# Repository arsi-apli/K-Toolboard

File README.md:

# K-Toolboard

3d printer toolboad for Klipper firmware. 
The toolboard consists of the injector board and the toolboard itself. 
An RPI FFC camera cable is used for the connection.
RS422 line is used for transmission and it is connected to the serial / USB converter on the injector board.

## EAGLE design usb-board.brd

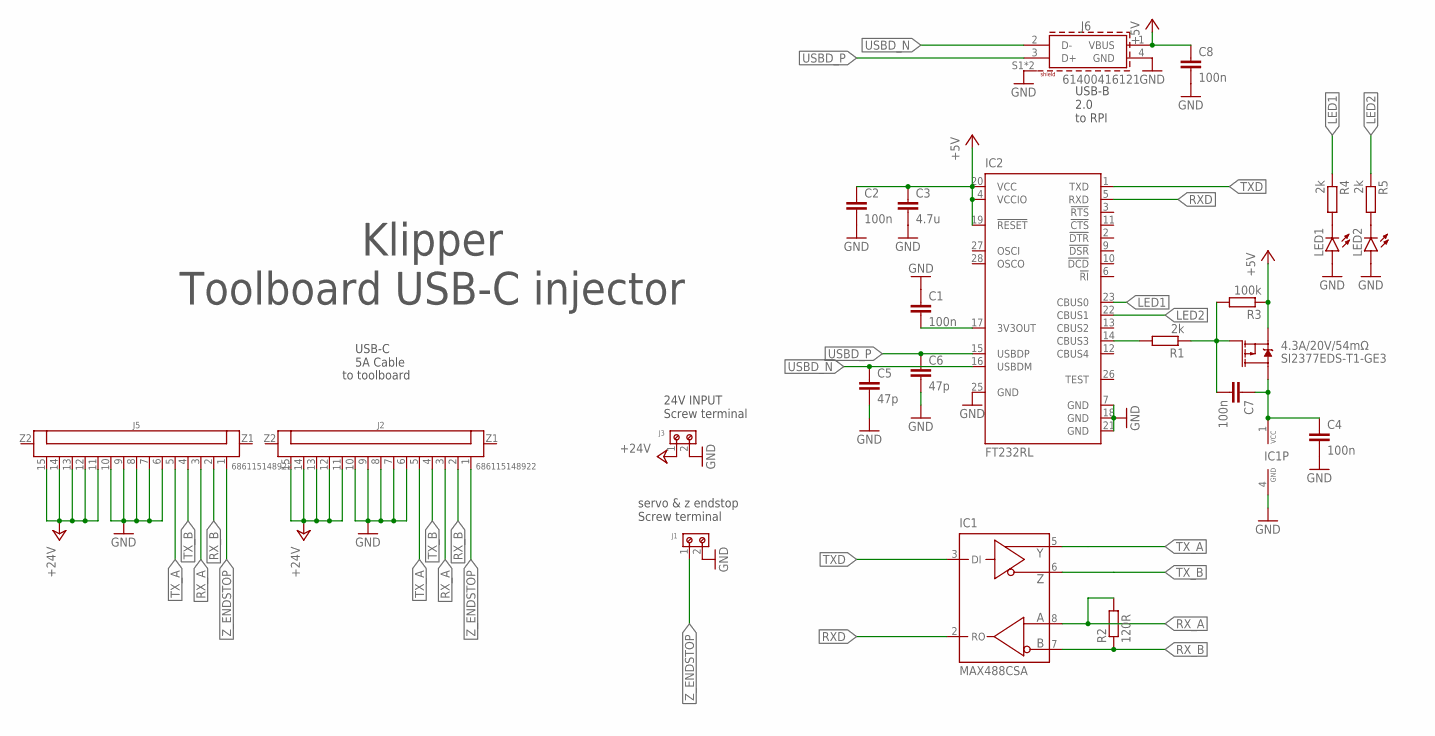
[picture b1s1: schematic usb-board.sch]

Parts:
C1, C2, C4, C7, C8: 100n; C0805
C3: 4.7u; C0805
C5, C6: 47p; C0805
IC1: MAX488CSA; SO08
IC2: FT232RL; SSOP28
J1, J3: 691103110002
J2, J5: 686115148922
J6: 61400416121
LED1, LED2: LEDCHIPLED_0805; CHIPLED_0805
R1, R4, R5: 2k; R0805
R2: 120R; R0805
R3: 100k; R0805
SI2377EDS-T1-GE3: 4.3A/20V/54mΩ; SOT23-3

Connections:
+5V: C2.1, C3.1, C8.1, IC2.4 (VCCIO), IC2.19 (!RESET), IC2.20 (VCC), J6.1 (VBUS), R3.1, SI2377EDS-T1-GE3.2 (S)
+24V: J2.11, J2.12, J2.13, J2.14, J2.15, J3.1, J5.11, J5.12, J5.13, J5.14, J5.15
GND: C1.1, C2.2, C3.2, C4.2, C5.2, C6.2, C8.2, IC1.4 (GND), IC2.7 (GND), IC2.18 (GND), IC2.21 (GND), IC2.25 (GND), J1.2, J2.6, J2.7, J2.8, J2.9, J2.10, J3.2, J5.6, J5.7, J5.8, J5.9, J5.10, J6.4 (GND), J6.S1 (SHIELD), J6.S2 (SHIELD), LED1.A, LED2.A
LED1: IC2.23 (CBUS0), R4.1
LED2: IC2.22 (CBUS1), R5.1
unnamed: C1.2, IC2.17 (3V3OUT)
unnamed: IC2.14 (CBUS3), R1.2
unnamed: C7.2, R1.1, R3.2, SI2377EDS-T1-GE3.1 (G)
unnamed: C4.1, C7.1, IC1.1 (VCC), SI2377EDS-T1-GE3.3 (D)
unnamed: LED1.C, R4.2
unnamed: LED2.C, R5.2
RXD: IC1.2 (RO), IC2.5 (RXD)
RX_A: IC1.8 (A), J2.3, J5.3, R2.2
RX_B: IC1.7 (B), J2.2, J5.2, R2.1
TXD: IC1.3 (DI), IC2.1 (TXD)
TX_A: IC1.5 (Y), J2.5, J5.5
TX_B: IC1.6 (Z), J2.4, J5.4
USBD_N: C5.1, IC2.16 (USBDM), J6.2 (D-)
USBD_P: C6.1, IC2.15 (USBDP), J6.3 (D+)
Z_ENDSTOP: J1.1, J2.1, J5.1

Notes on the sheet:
USB-C 5A Cable
to toolboard
24V INPUT Screw terminal
servo & z endstop Screw terminal
Klipper Toolboard USB-C injector
USB-B 2.0 to RPI

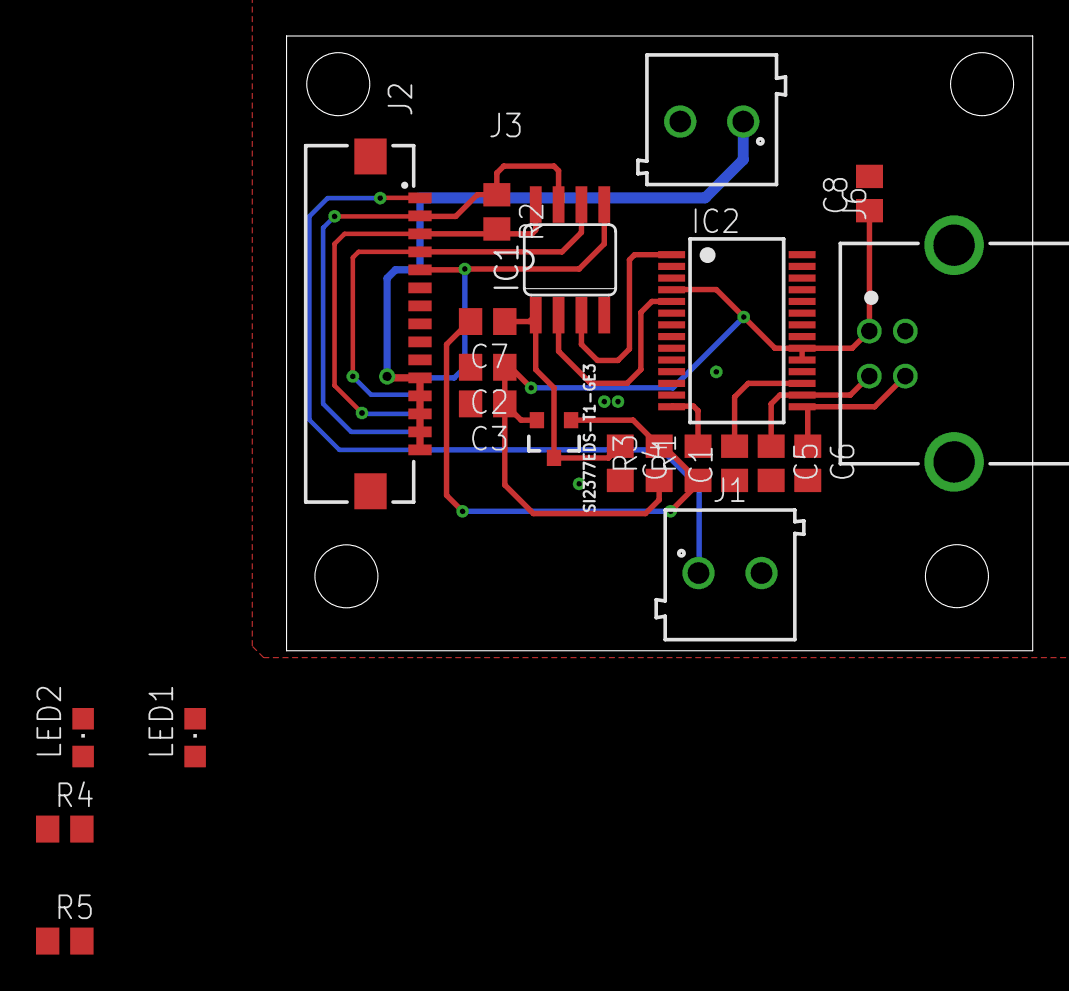
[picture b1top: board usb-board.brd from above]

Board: 2 copper layers, 41.5 x 34.2 mm, 23 parts (1 on the bottom side), 20 nets.

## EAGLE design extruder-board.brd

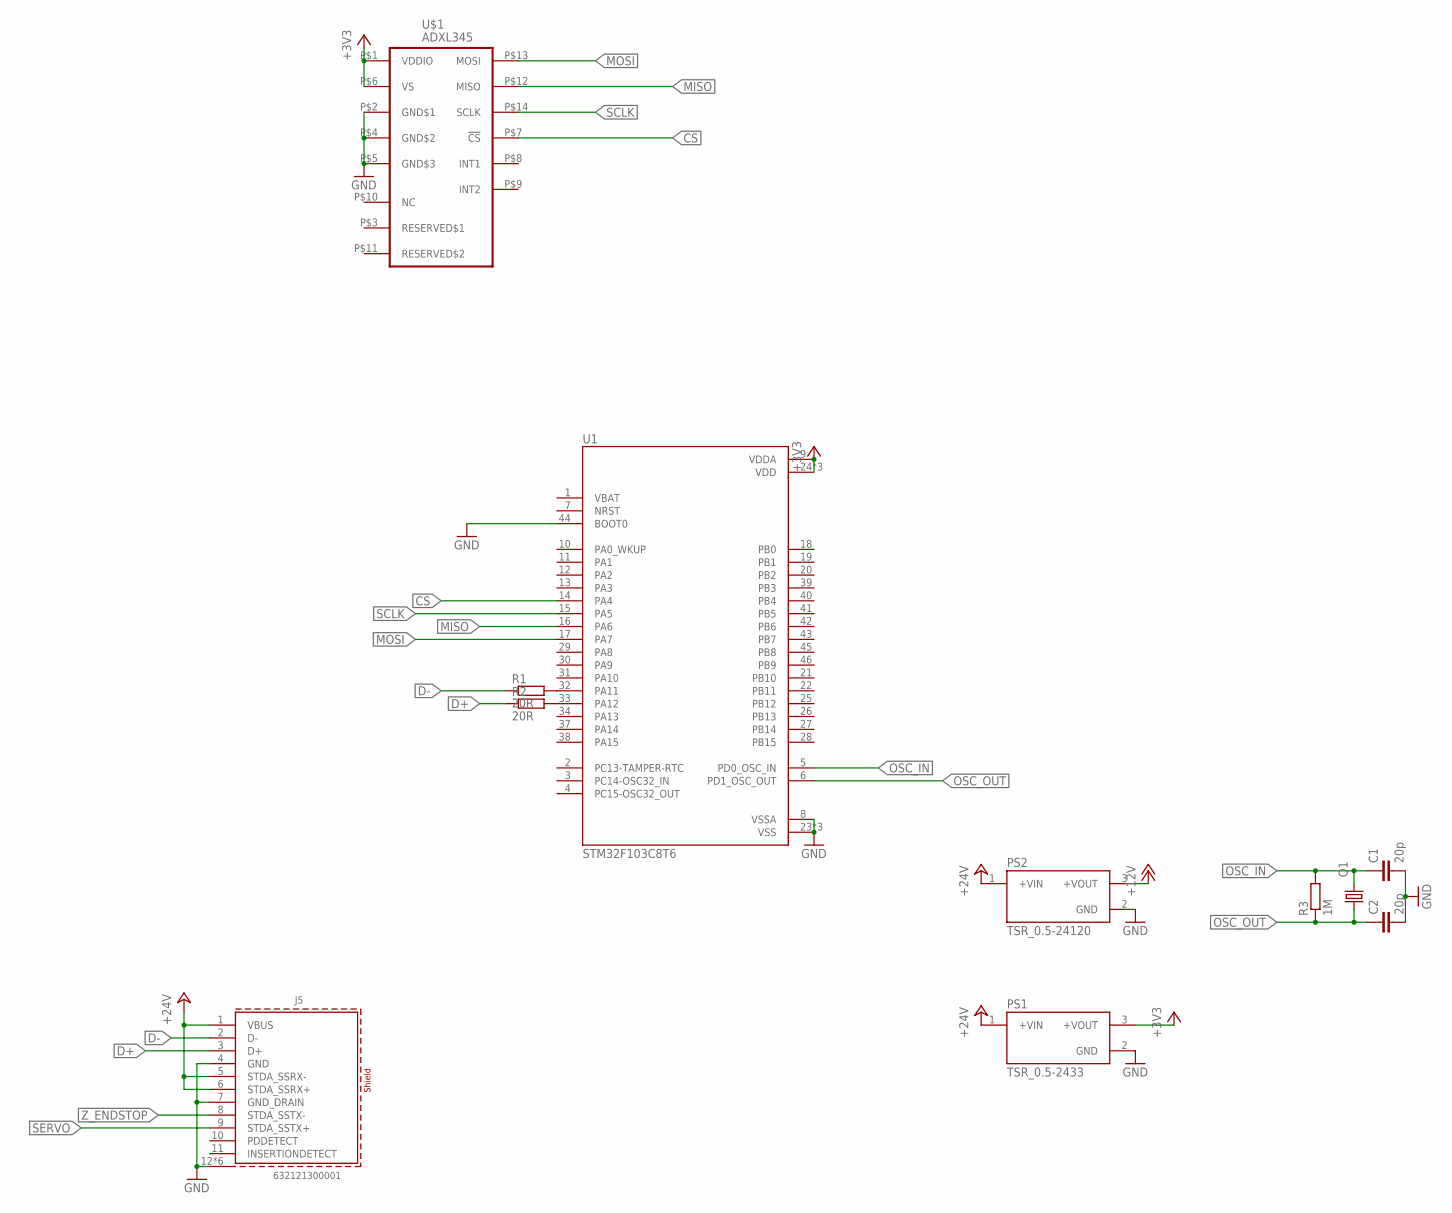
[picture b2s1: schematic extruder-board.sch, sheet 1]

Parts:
C1, C2: 20p; C0805
J5: 632121300001
PS1: TSR_0.5-2433; CONV_TSR_0.5-2433
PS2: TSR_0.5-24120; CONV_TSR_0.5-2433
Q1: KX-9A; 5.0X3.2_KX-9A
R1, R2: 20R; R0805
R3: 1M; R0805
U1: STM32F103C8T6; QFP50P900X900X160-48N
U$1: ADXL345; LGA14

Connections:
+3V3: PS1.3 (+VOUT), U1.9 (VDDA), U1.24 (VDD), U1.36 (VDD), U1.48 (VDD), U$1.P$1 (VDDIO), U$1.P$6 (VS)
+12V: PS2.3 (+VOUT)
+24V: J5.1 (VBUS), J5.5 (STDA_SSRX-), J5.6 (STDA_SSRX+), PS1.1 (+VIN), PS2.1 (+VIN)
CS: U1.14 (PA4), U$1.P$7 (!CS)
D+: J5.3 (D+), R2.1
D-: J5.2 (D-), R1.1
GND: C1.2, C2.2, J5.4 (GND), J5.7 (GND_DRAIN), J5.12 (SHIELD), J5.13 (SHIELD), J5.S1 (SHIELD), J5.S2 (SHIELD), J5.S3 (SHIELD), J5.S4 (SHIELD), PS1.2 (GND), PS2.2 (GND), U1.8 (VSSA), U1.23 (VSS), U1.35 (VSS), U1.44 (BOOT0), U1.47 (VSS), U$1.P$2 (GND$1), U$1.P$4 (GND$2), U$1.P$5 (GND$3)
MISO: U1.16 (PA6), U$1.P$12 (MISO)
MOSI: U1.17 (PA7), U$1.P$13 (MOSI)
unnamed: R1.2, U1.32 (PA11)
unnamed: R2.2, U1.33 (PA12)
OSC_IN: C1.1, Q1.3 (2), R3.2, U1.5 (PD0_OSC_IN)
OSC_OUT: C2.1, Q1.1, R3.1, U1.6 (PD1_OSC_OUT)
SCLK: U1.15 (PA5), U$1.P$14 (SCLK)
SERVO: J5.9 (STDA_SSTX+)
Z_ENDSTOP: J5.8 (STDA_SSTX-)

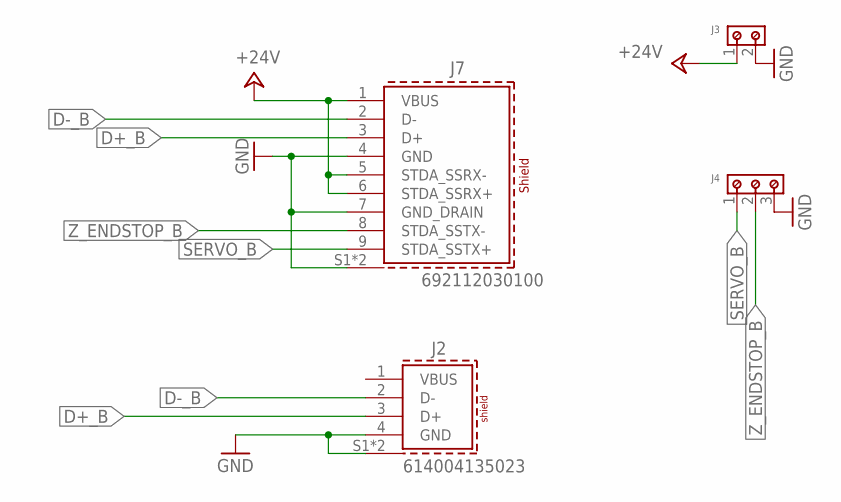
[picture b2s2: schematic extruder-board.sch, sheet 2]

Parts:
J2: 614004135023
J3: 691103110002
J4: 691103110003
J7: 692112030100

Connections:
+24V_B: J3.1, J7.1 (VBUS), J7.5 (STDA_SSRX-), J7.6 (STDA_SSRX+)
D+_B: J2.3 (D+), J7.3 (D+)
D-_B: J2.2 (D-), J7.2 (D-)
GND_B: J2.4 (GND), J2.S1 (SHIELD), J2.S2 (SHIELD), J3.2, J4.3, J7.4 (GND), J7.7 (GND_DRAIN), J7.S1 (SHIELD), J7.S2 (SHIELD)
SERVO_B: J4.1, J7.9 (STDA_SSTX+)
Z_ENDSTOP_B: J4.2, J7.8 (STDA_SSTX-)

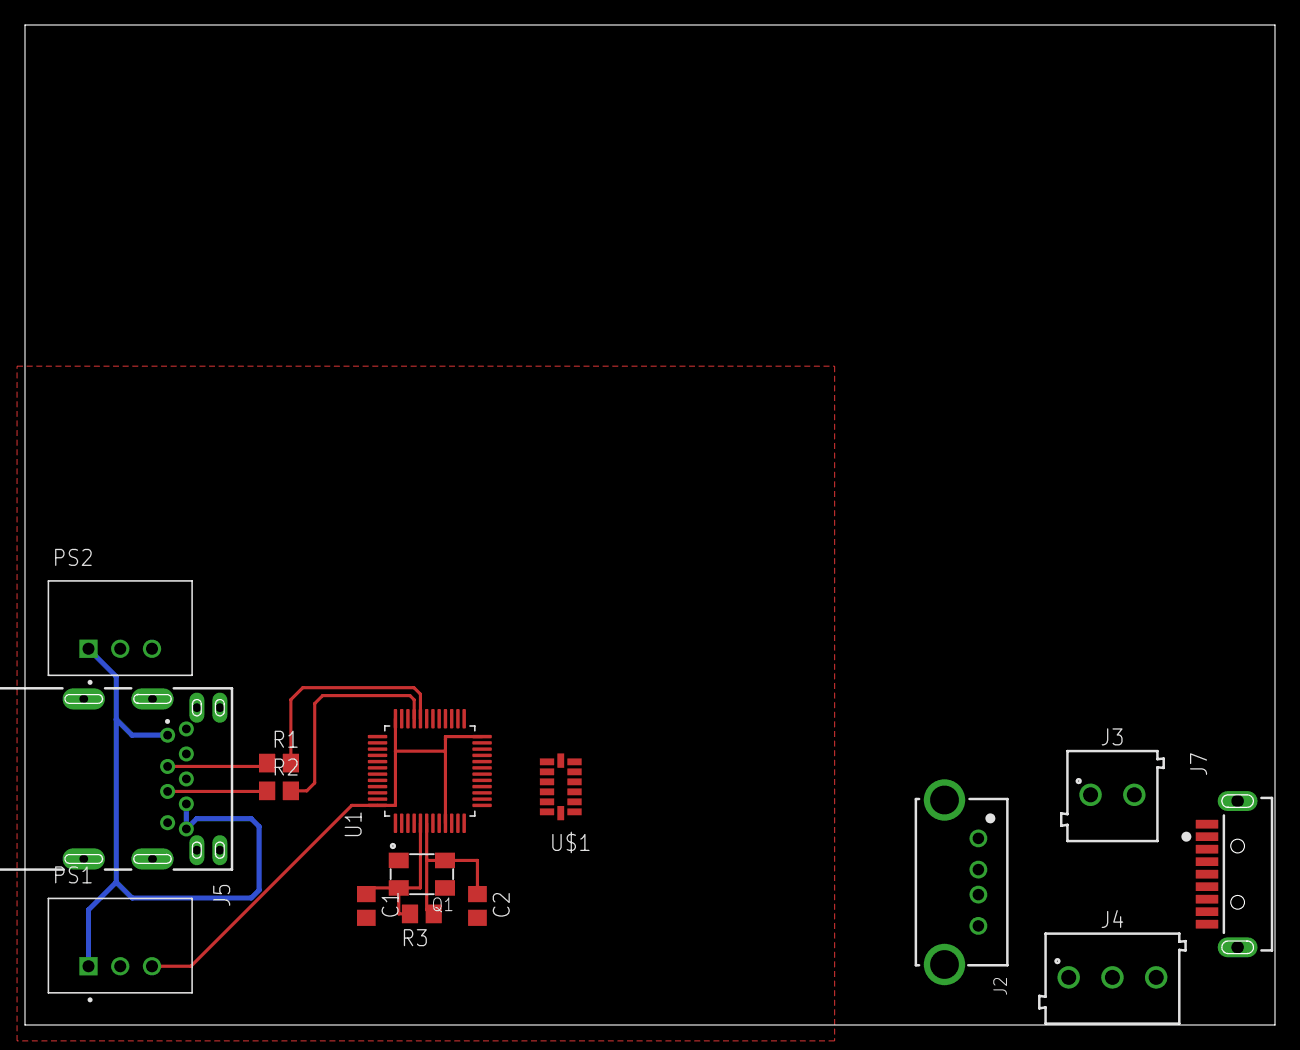
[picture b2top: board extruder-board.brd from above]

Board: 2 copper layers, 100.0 x 80.0 mm, 15 parts (0 on the bottom side), 19 nets.

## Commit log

2021-08-28 added library export
2021-08-28 Readme + pdf export of injector board

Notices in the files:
parts and their libraries:
Eagle_WR-USB: Copyright: Würth Elektronik
crystal-geyer_V1_0: Copyright: Geyer-Electronic
SparkFun-DiscreteSemi: Licensing: Creative Commons ShareAlike 4.0 International - https://creativecommons.org/licenses/by-sa/4.0
